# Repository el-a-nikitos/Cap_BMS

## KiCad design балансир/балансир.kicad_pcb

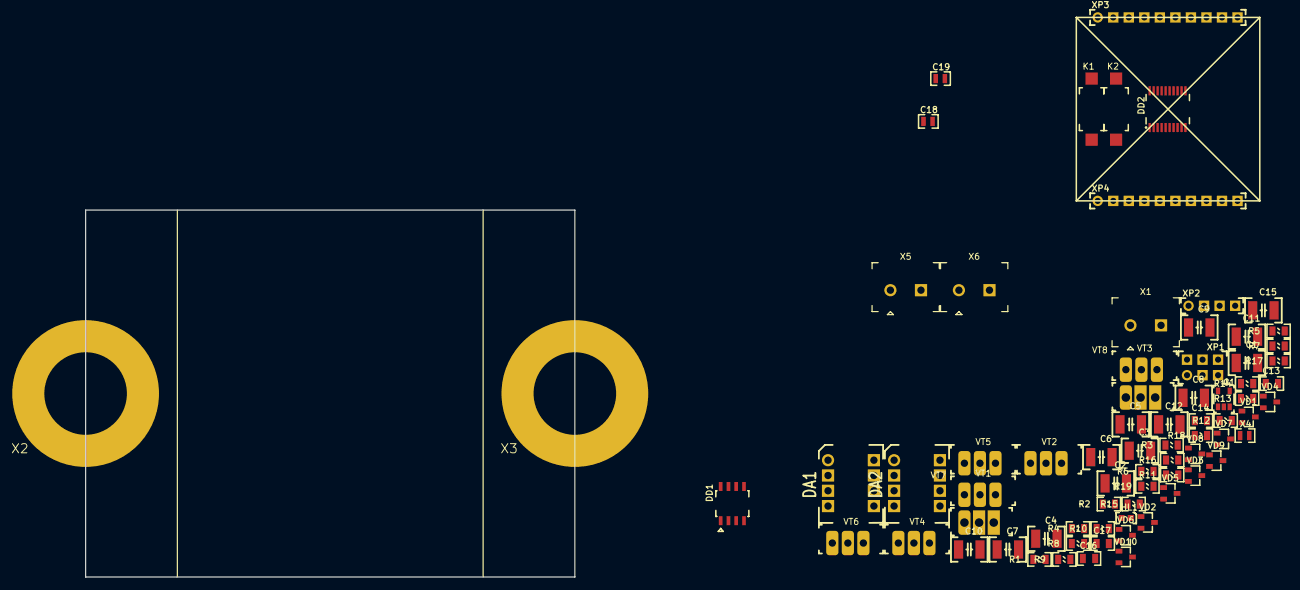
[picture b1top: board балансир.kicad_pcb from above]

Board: 2 copper layers, 80.0 x 60.0 mm, 74 parts (0 on the bottom side), 40 nets, no tracks yet.

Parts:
C1, C2, C3, C4, C5, C6, C7, C8, C9, C10, C11, C12, C15: 4.7мкФ, 1210; Конденсатор_SMD_1210
C13, C14, C16, C17: 4.7мкФ, 0805; Конденсатор_SMD_0805
C18, C19: 12Ф, 0603; Конденсатор_SMD_0603
DA1, DA2: МОП-реле_КР293КП4; DIP8
DD1: 5559ИН10_28(UART-RS485); SO-8
DD2: STM32F030F4P6(TSSOP-20); SSOP-20
G1: стабилизатор_нерегулируемый_MC78LC33NTRG; Преобразователь_LM2703_SOT-23-5
HL1: Светодиод; Светодиод_SMD_0603
K1, K2: 1437566-3 (FSMSM); Кнопка_FSMSM
R1, R2, R3, R4, R5, R6, R7, R8, R9, R10, R11, R12, R14, R15, R17, R18, R19: Резистор_0,125Вт; Резистор_SMD_0805_0,125Вт
R13, R16: 20к, 0805; Резистор_SMD_0805_0,125Вт
VD1, VD2, VD3, VD4, VD5, VD6, VD7, VD8, VD9, VD10: Диод_шоттки(2-анод); Диод_BAR43CFILM_SOT-23
VT1, VT2, VT3, VT4, VT5, VT6: Транзистор_полевой_P-канал; Транзистор_P_IRF9Z24NPBF
VT7, VT8: Транзистор_полевой_N-канал; Транзистор_N_STP10NK60Z
X1, X5, X6: Клеммник_х2; Клеммник_х2_шаг5
X2: Средняя точка(M12); Отверстие_М12
X3: Минус(M12); Отверстие_М12
X4: перемычка_разрывная; Конденсатор_SMD_0603
XP1: Вилка_PLD6_ПРОГ; Вилка_PLD6_вертикальная
XP2: Вилка_PLS4; Вилка_PLS4_вертикальная
XP3, XP4: Вилка_PLS10; Вилка_PLS10_вертикальная

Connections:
/0В: C14.2, C16.2, C17.2, C18.2, C19.2, DA1.1, DA2.1, DD2.15, G1.1, HL1.2, K2.2, R7.2, R8.2, R9.2, R13.1, R19.2, VD9.1, VT7.2, X3.1, XP1.6, XP2.3, XP3.6
/+3В: C13.1, R5.1, R6.1, VD3.2, VD5.2, VD7.2, VT3.2, VT5.2, X2.1
/+5В_эфир: C15.1, DD1.8, X6.1
/+6В: G1.2, R4.1, VD1.2, VT1.2, X1.1, X1.2
/A: DD1.6, X5.1
/ADC5_6V: DD2.14, R4.2, R7.1, XP3.7
/ADCT2: C14.1, DD2.11, R6.2, XP3.10
/ADC_3V: DD2.13, R5.2, R8.1, XP3.8
/ADC_T1: C13.2, DD2.12, R9.1, XP3.9
/B: DD1.7, X5.2
/BOOT_mode: DD2.1, K1.1, R13.2, XP1.4, XP4.1
/CLK: DD2.20, XP1.3, XP3.1
/DIO: DD2.19, XP1.1, XP3.2
/EnRS: DD2.10, R17.2, XP4.10
/EnRS_ext: DA2.7, DD1.2, DD1.3, R14.1
/G1: DD2.7, R10.2, VT7.1, VT8.1, XP4.7
/G2: DD2.6, R3.2, VT5.1, VT6.1, XP4.6
/G3: C19.1, DD2.3, R2.2, VT3.1, VT4.1, XP4.3
/G4: C18.1, DD2.2, R1.2, VT1.1, VT2.1, XP4.2
/GND_эфир: C15.2, DA1.4, DD1.5, R14.2, R15.2, X6.2
/RES: DD2.4, K2.1, R16.2, XP1.5, XP4.4
/RX: DA1.6, DD2.9, R19.1, XP4.9
/RX_ext: DD1.1, R12.2
/RXboot_SDA: DD2.18, XP2.1, XP3.3
/TX: DD2.8, R11.2, XP4.8
/TX_ext: DA1.7, DD1.4, R15.1
/TXboot_SCL: DD2.17, XP2.2, XP3.4
/VCC: C16.1, C17.1, DA1.8, DA2.8, DD2.5, DD2.16, G1.3, K1.2, R16.1, VD7.1, VD8.1, X4.2, XP2.4, XP3.5, XP4.5
/VCCprog: VD8.2, XP1.2
unnamed: C1.1, C2.1, C3.1, C4.1, C5.1, C6.1, C7.1, C8.1, C9.1, C10.1, C11.1, C12.1, VD2.2, VD4.2, VT2.2, VT4.2
unnamed: C1.2, C2.2, C3.2, C4.2, C5.2, C6.2, C7.2, C8.2, C9.2, C10.2, C11.2, C12.2, VD6.2, VD10.1, VT6.2, VT8.2
unnamed: DA1.2, R11.1
unnamed: DA1.3, R12.1
unnamed: DA2.2, R17.1
unnamed: HL1.1, R18.2
unnamed: R1.1, VD1.1, VD2.1, VT1.3, VT2.3
unnamed: R2.1, VD3.1, VD4.1, VT3.3, VT4.3
unnamed: R3.1, VD5.1, VD6.1, VT5.3, VT6.3
unnamed: R10.1, VD9.2, VD10.2, VT7.3, VT8.3
unnamed: R18.1, X4.1

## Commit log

2019-01-29 проект платы балансира активного
2019-01-30 есть схема, но нет решения по связи
2019-02-19 добавлена STM32
2019-02-20 не решен вопрос стабильного питания, не убран старый контроллер
2019-02-21 atmega8 заменена на stm32 разводка не готова
